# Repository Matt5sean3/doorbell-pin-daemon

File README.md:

# Doorbell Pin Daemon

This is a simple program for controlling a Doorbell using a Raspberry Pi. With minor modifications this system should be usable with any Linux system that can control GPIOs via sysfs. Everything from board designs to the systemd service are included. This is still in development and ideally will be deployable as just a debian package on the Pi eventually.

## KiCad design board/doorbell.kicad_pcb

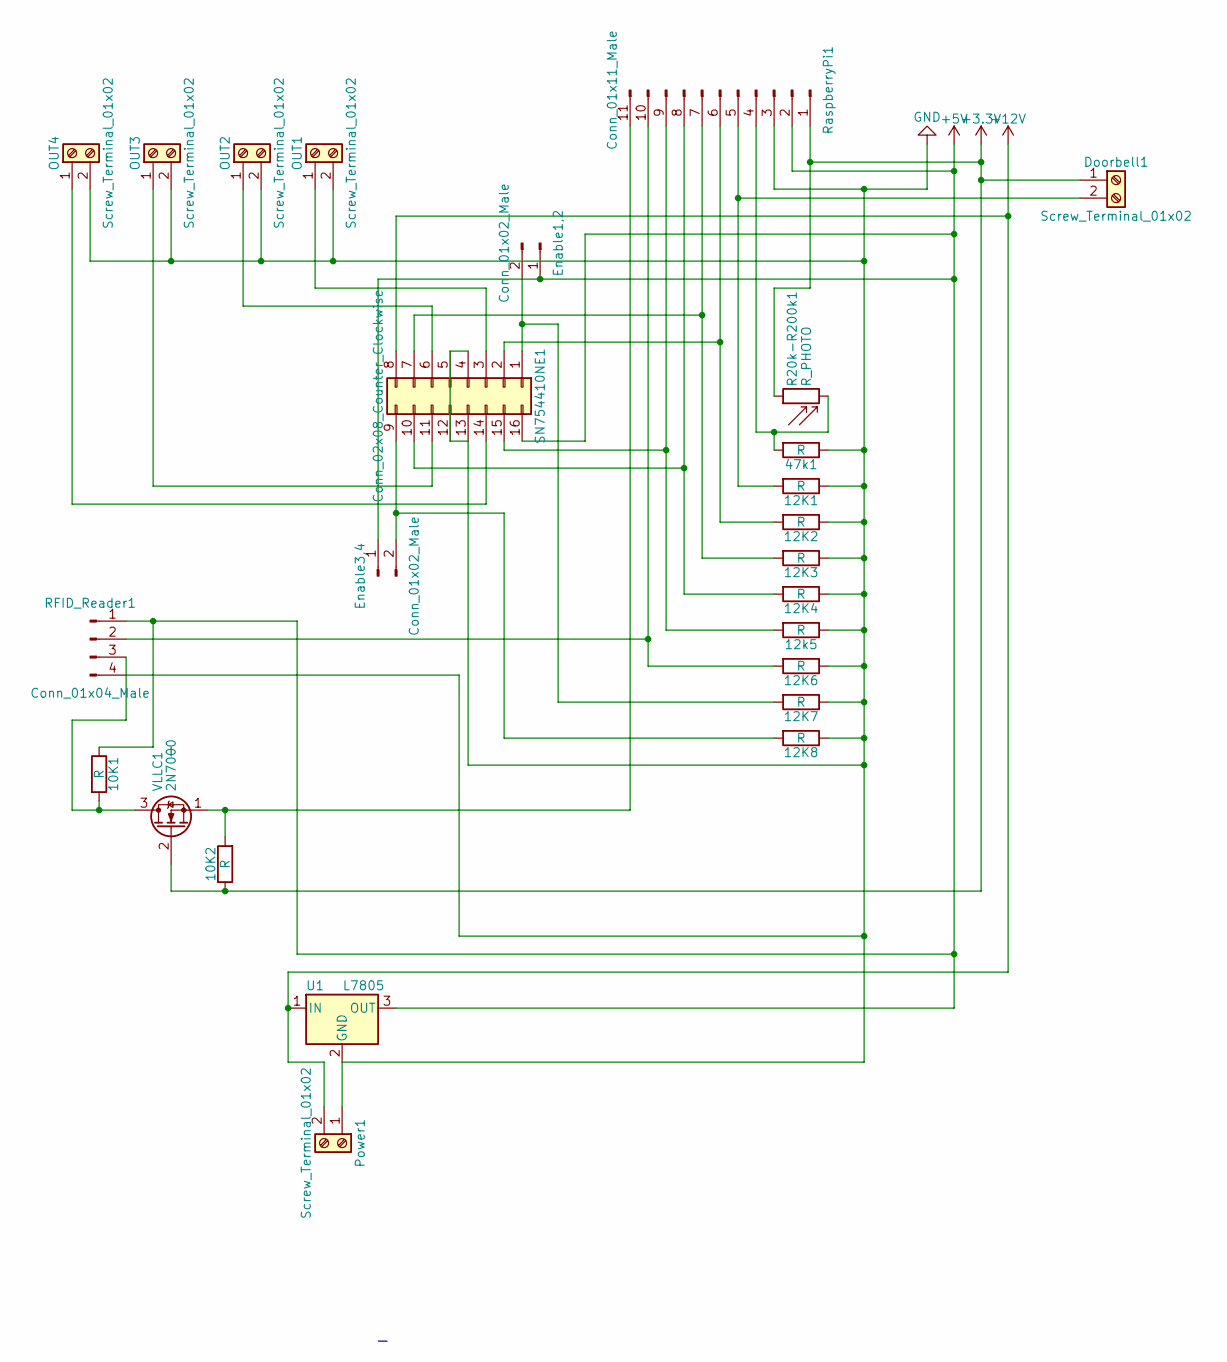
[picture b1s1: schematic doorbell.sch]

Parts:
10K1, 10K2: R; R_Axial_DIN0204_L3.6mm_D1.6mm_P7.62mm_Horizontal
12K1, 12K2, 12K3, 12K4, 12K6, 12K7, 12K8, 12k5, 47k1: R; R_Axial_DIN0207_L6.3mm_D2.5mm_P7.62mm_Horizontal
Doorbell1: Screw_Terminal_01x02; TerminalBlock_Philmore_TB132_02x5mm_Straight
Enable1,2, Enable3,4: Conn_01x02_Male; Pin_Header_Straight_1x02_Pitch2.54mm
OUT1, OUT2, OUT3, OUT4: Screw_Terminal_01x02; TerminalBlock_Philmore_TB132_02x5mm_Straight
Power1: Screw_Terminal_01x02; TerminalBlock_Philmore_TB132_02x5mm_Straight
R20k-R200k1: R_PHOTO; R_Axial_DIN0204_L3.6mm_D1.6mm_P5.08mm_Vertical
RFID_Reader1: Conn_01x04_Male; Pin_Header_Straight_1x04_Pitch2.54mm
RaspberryPi1: Conn_01x11_Male; Pin_Header_Straight_1x11_Pitch2.54mm
SN754410NE1: Conn_02x08_Counter_Clockwise; DIP-16_W7.62mm
U1: L7805; TO-220
VLLC1: 2N7000; TO-92_Inline_Wide

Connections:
+3V3: 10K2.1, Doorbell1.1, R20k-R200k1.1, RaspberryPi1.1, VLLC1.2 (G)
+5V: 10K1.1, Enable1,2.1, Enable3,4.1, RFID_Reader1.1, RaspberryPi1.2, SN754410NE1.16, U1.3 (OUT)
+12V: Power1.2, SN754410NE1.8, U1.1 (IN)
GND: 12K1.1, 12K2.1, 12K3.1, 12K4.1, 12K6.1, 12K7.1, 12K8.1, 12k5.1, 47k1.1, OUT1.2, OUT2.2, OUT3.2, OUT4.2, Power1.1, RFID_Reader1.4, RaspberryPi1.3, SN754410NE1.4, SN754410NE1.5, SN754410NE1.12, SN754410NE1.13, U1.2 (GND)
unnamed: 10K1.2, RFID_Reader1.3, VLLC1.3 (D)
unnamed: 10K2.2, RaspberryPi1.11, VLLC1.1 (S)
unnamed: 12K1.2, Doorbell1.2, RaspberryPi1.5
unnamed: 12K2.2, RaspberryPi1.6, SN754410NE1.2
unnamed: 12K3.2, RaspberryPi1.7, SN754410NE1.7
unnamed: 12K4.2, RaspberryPi1.8, SN754410NE1.10
unnamed: 12K6.2, RFID_Reader1.2, RaspberryPi1.10
unnamed: 12K7.2, Enable1,2.2, SN754410NE1.1
unnamed: 12K8.2, Enable3,4.2, SN754410NE1.9
unnamed: 12k5.2, RaspberryPi1.9, SN754410NE1.15
unnamed: 47k1.2, R20k-R200k1.2, RaspberryPi1.4
unnamed: OUT1.1, SN754410NE1.3
unnamed: OUT2.1, SN754410NE1.6
unnamed: OUT3.1, SN754410NE1.11
unnamed: OUT4.1, SN754410NE1.14

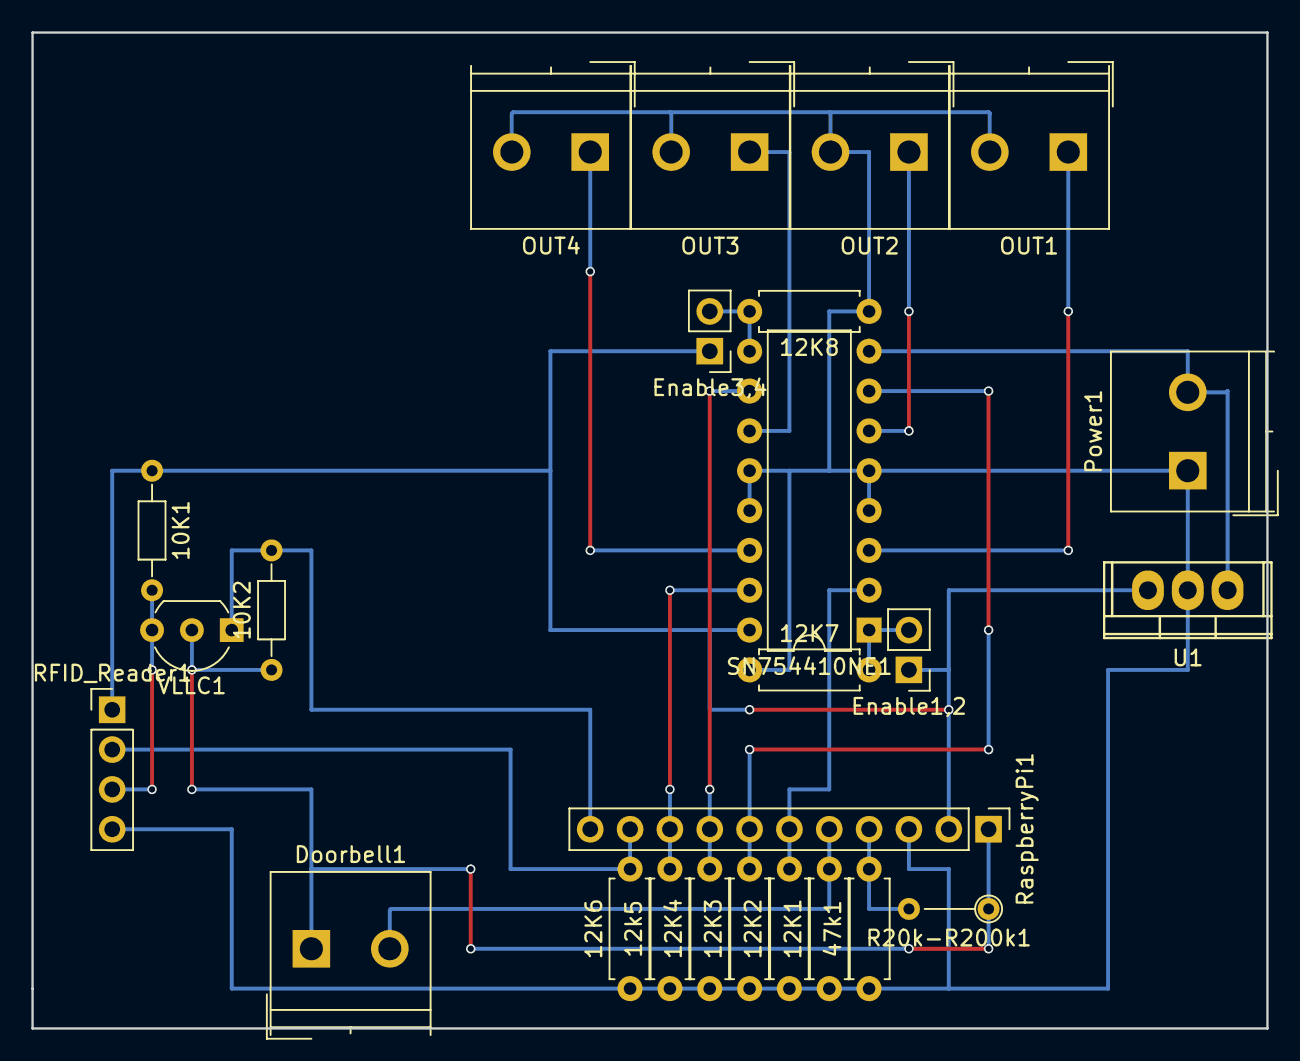
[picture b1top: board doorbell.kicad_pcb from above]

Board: 2 copper layers, 78.7 x 63.5 mm, 25 parts (0 on the bottom side), 19 nets.

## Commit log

2017-10-08 First commit in half-working state, just rings the doorbell, holding for a second
2017-10-09 First version with a fully working doorbell
2017-10-09 Added functionality for logging light levels
2017-11-02 Add board design files
2017-11-10 Created enclosure design
2017-11-21 Modified data structures to include info about uart ports
2017-11-21 Better namespacing for enums
2017-11-22 Changed pin configuration to use pins toward the top of the board
2017-11-22 Added README and added the template for the service
2017-11-22 Fixed format of light log file
2017-12-22 Implemented basic handling of RFID
2017-12-22 Switched file manipulation for sockets from stdio to unix reads
2017-12-22 RFID reading should work, need to test, FIFOs are in the works
2017-12-23 Specifying project language as C
2017-12-26 Adding test code
2017-12-27 Reading RFID now works
2017-12-28 Dings when RFID tags are read
2018-01-20 Added macros for better readability and disabled ringing when RFID tags are read
